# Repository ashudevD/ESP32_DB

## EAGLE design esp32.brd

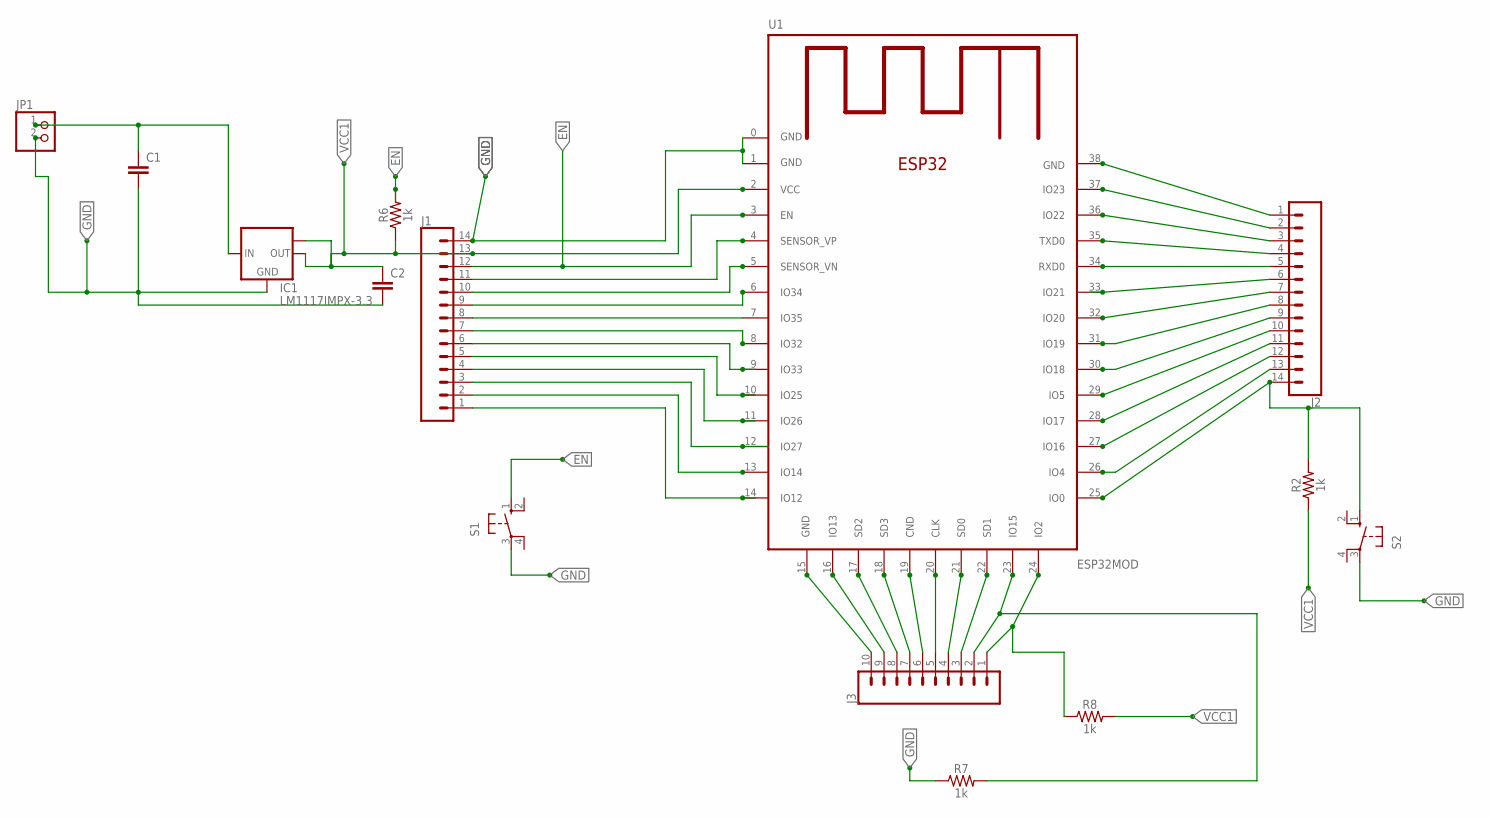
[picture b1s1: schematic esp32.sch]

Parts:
C1, C2: C-EU025-050X050; C025-050X050
IC1: LM1117IMPX-3.3; SOT223
J1, J2: CONN_14LONGPADS; 1X14-LONGPADS
J3: CONN_10"; 1X10
JP1: PINHD-1X2; 1X02
R2, R6, R7, R8: 1k; AXIAL-0.3
S1, S2: 10-XX; B3F-10XX
U1: ESP32MOD

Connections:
EN: J1.12, R6.P$2 (2), S1.1 (S), U1.3 (EN)
GND: C1.2, C2.2, IC1.1 (GND), J1.14, J2.1, J3.10, JP1.2, R7.P$1 (1), S1.3, S2.3, U1.0 (GND), U1.1 (GND), U1.15 (GND), U1.38 (GND)
unnamed: J2.7, U1.32 (IO20)
unnamed: J1.11, U1.4 (SENSOR_VP)
unnamed: J1.10, U1.5 (SENSOR_VN)
unnamed: J2.14, R2.P$2 (2), S2.1 (S), U1.25 (IO0)
unnamed: J1.9, U1.6 (IO34)
unnamed: J1.8, U1.7 (IO35)
unnamed: J1.7, U1.8 (IO32)
unnamed: J1.6, U1.9 (IO33)
unnamed: J1.5, U1.10 (IO25)
unnamed: J1.4, U1.11 (IO26)
unnamed: J1.3, U1.12 (IO27)
unnamed: J1.2, U1.13 (IO14)
unnamed: J1.1, U1.14 (IO12)
unnamed: J2.5, U1.34 (RXD0)
unnamed: J2.4, U1.35 (TXD0)
unnamed: J2.3, U1.36 (IO22)
unnamed: J2.2, U1.37 (IO23)
unnamed: J2.10, U1.29 (IO5)
unnamed: J2.6, U1.33 (IO21)
unnamed: C1.1, IC1.3 (IN), JP1.1
unnamed: J2.8, U1.31 (IO19)
unnamed: J2.9, U1.30 (IO18)
unnamed: J2.11, U1.28 (IO17)
unnamed: J2.12, U1.27 (IO16)
unnamed: J2.13, U1.26 (IO4)
unnamed: J3.9, U1.16 (IO13)
unnamed: J3.8, U1.17 (SD2)
unnamed: J3.7, U1.18 (SD3)
unnamed: J3.6, U1.19 (CND)
unnamed: J3.5, U1.20 (CLK)
unnamed: J3.4, U1.21 (SD0)
unnamed: J3.3, U1.22 (SD1)
unnamed: J3.2, R7.P$2 (2), U1.23 (IO15)
unnamed: J3.1, R8.P$1 (1), U1.24 (IO2)
VCC1: C2.1, IC1.2 (OUT), IC1.TAB (OUT1), J1.13, R2.P$1 (1), R6.P$1 (1), R8.P$2 (2), U1.2 (VCC)

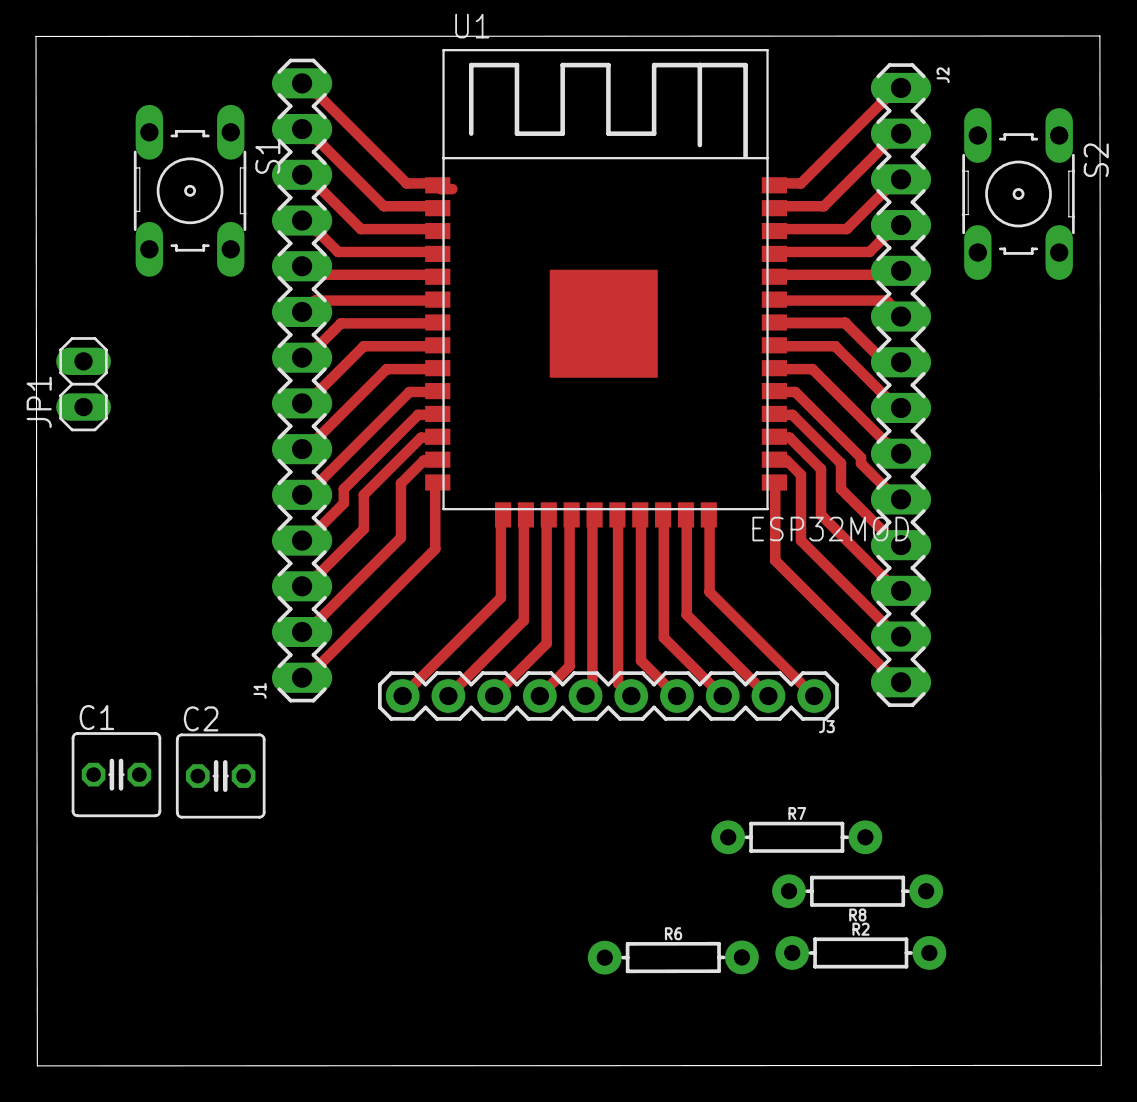
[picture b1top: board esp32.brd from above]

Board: 2 copper layers, 59.2 x 57.2 mm, 14 parts (1 on the bottom side), 37 nets.

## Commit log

2017-05-22 Work initiated
2017-05-23 Updated board file
2017-05-24 updated track and placing of AMS117 modified, peripheral: NA

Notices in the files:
parts and their libraries:
SparkFun-Connectors: Licensing: Creative Commons ShareAlike 4.0 International - https://creativecommons.org/licenses/by-sa/4.0
